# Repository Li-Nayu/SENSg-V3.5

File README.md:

SENSg-V3.5
==========
<h4>National Science Experiment: SENsg,  Large-scale Internet of Things Sensor Deployment in SUTD, Singapore</h4>

#Overview
V3.5 of SENSg is developed during my exchange period in SUTD, Singapore. Thanks to Professor Wilhelm Erik's kind guidance.

#Change Log
* Add P-channel MOSFET as the power switch for camera. MOSFET is controlled by MCU pin1, which is also the LDR sensor's GPIO pin. 
* With a pull-up resistor, the camera won't on unless the pin1 gives a low voltage. Also the camera's VCC input is changed to MOSFET's source.
* All changes were tested.

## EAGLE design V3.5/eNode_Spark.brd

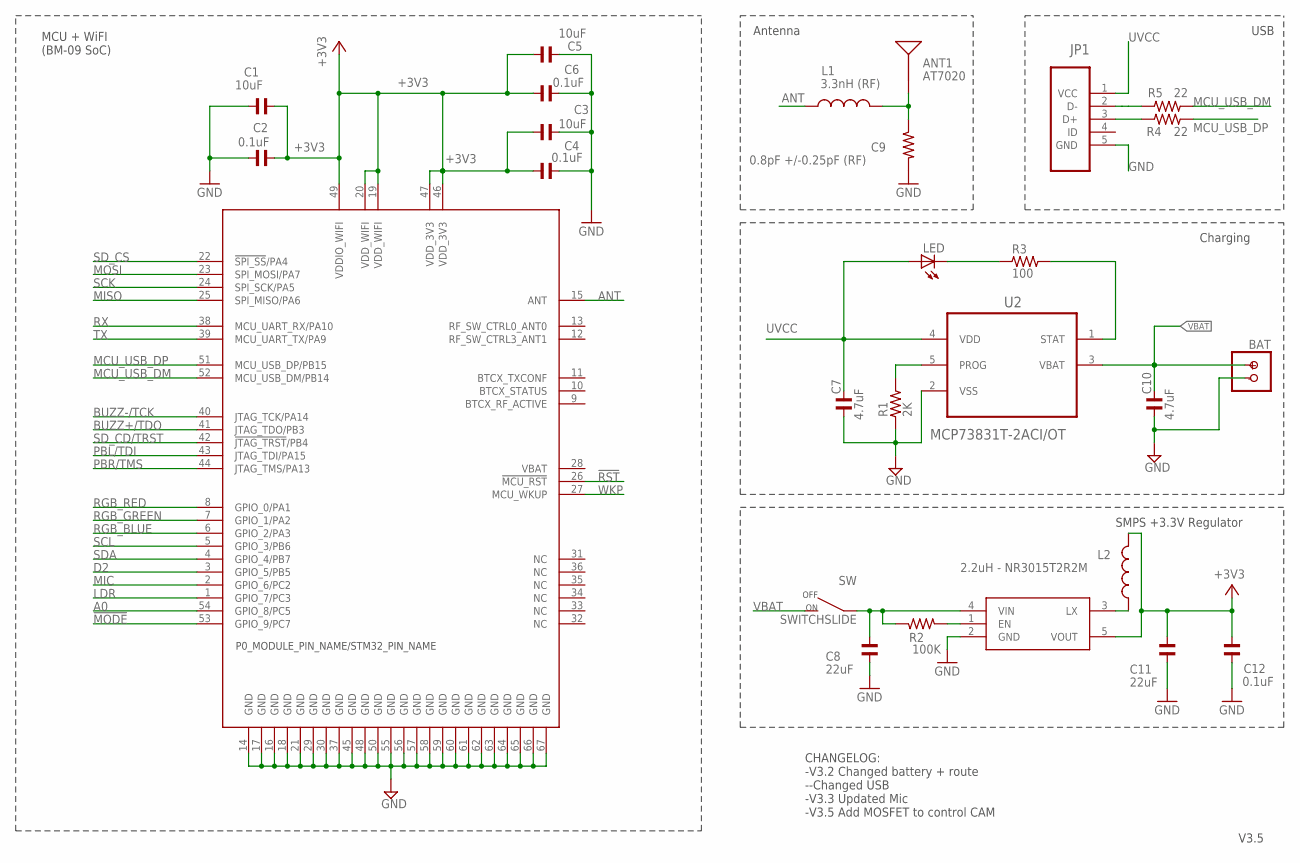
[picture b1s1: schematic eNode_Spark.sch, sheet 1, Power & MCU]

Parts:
ANT1: AT7020
BAT: BATTERYSMT; JST-2-SMD
C1, C3, C5: 10uF; C0402
C2, C4, C6, C12: 0.1uF; C0402
C7, C10: 4.7uF; C0402
C8, C11: 22uF; C0603
C9: 0.8pF +/-0.25pF (RF); R0402_B
JP1: 47346-0001; MOLEX_47346-0001
L1: 3.3nH (RF); L0402_B
L2: 2.2uH - NR3015T2R2M; INDUCTOR-NR3015
LED: LED; SMARTLED-TTW
R1: 2K; R0603
R2: 100K; R0402
R3: 100; R0603
R4, R5: 22; R0402
SW: SWITCHSLIDE; CHANGE_OVER_SLIDE
U1: WM-N-BM-09
U2: MCP73831T-2ACI/OT; SOT95P280X145-5N
U3: R8008-33; SOT23-5

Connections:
!MODE: U1.53 (GPIO_9/PC7); also elsewhere on the board
!RST: U1.26 (!MCU_RST); also elsewhere on the board
+3V3: C1.2, C2.2, C3.1, C4.2, C5.1, C6.2, C11.1, C12.1, L2.2, U1.19 (VDD_WIFI), U1.20 (VDD_WIFI), U1.46 (VDD_3V3), U1.47 (VDD_3V3), U1.49 (VDDIO_WIFI), U3.5 (VOUT); also elsewhere on the board
A0: U1.54 (GPIO_8/PC5)
ANT: L1.1, U1.15 (ANT)
BUZZ+/TDO: U1.41 (JTAG_TDO/PB3); also elsewhere on the board
BUZZ-/TCK: U1.40 (JTAG_TCK/PA14); also elsewhere on the board
D2: U1.3 (GPIO_5/PB5); also elsewhere on the board
ENABLE: R2.1, U3.1 (EN)
GND: BAT.-, C1.1, C2.1, C3.2, C4.1, C5.2, C6.1, C7.1, C8.2, C9.2, C10.1, C11.2, C12.2, JP1.5 (GND), R1.1, U1.14 (GND), U1.16 (GND), U1.17 (GND), U1.18 (GND), U1.21 (GND), U1.29 (GND), U1.30 (GND), U1.37 (GND), U1.45 (GND), U1.48 (GND), U1.50 (GND), U1.55 (GND), U1.56 (GND), U1.57 (GND), U1.58 (GND), U1.59 (GND), U1.60 (GND), U1.61 (GND), U1.62 (GND), U1.63 (GND), U1.64 (GND), U1.65 (GND), U1.66 (GND), U1.67 (GND), U2.2 (VSS), U3.2 (GND); also elsewhere on the board
LDR: U1.1 (GPIO_7/PC3); also elsewhere on the board
MCU_USB_DM: R5.1, U1.52 (MCU_USB_DM/PB14)
MCU_USB_DP: R4.1, U1.51 (MCU_USB_DP/PB15)
MIC: U1.2 (GPIO_6/PC2); also elsewhere on the board
MISO: U1.25 (SPI_MISO/PA6); also elsewhere on the board
MOSI: U1.23 (SPI_MOSI/PA7); also elsewhere on the board
unnamed: ANT1.1, C9.1, L1.2
unnamed: C8.1, R2.2, SW.1, U3.4 (VIN)
unnamed: L2.1, U3.3 (LX)
unnamed: R1.2, U2.5 (PROG)
unnamed: LED.C@1 (C), R3.1
unnamed: R3.2, U2.1 (STAT)
unnamed: JP1.3 (D+), R4.2
unnamed: JP1.2 (D-), R5.2
PBL/TDI: U1.43 (JTAG_TDI/PA15); also elsewhere on the board
PBR/TMS: U1.44 (JTAG_TMS/PA13); also elsewhere on the board
RGB_BLUE: U1.6 (GPIO_2/PA3); also elsewhere on the board
RGB_GREEN: U1.7 (GPIO_1/PA2); also elsewhere on the board
RGB_RED: U1.8 (GPIO_0/PA1); also elsewhere on the board
RX: U1.38 (MCU_UART_RX/PA10); also elsewhere on the board
SCK: U1.24 (SPI_SCK/PA5); also elsewhere on the board
SCL: U1.5 (GPIO_3/PB6); also elsewhere on the board
SDA: U1.4 (GPIO_4/PB7); also elsewhere on the board
SD_CD/TRST: U1.42 (!JTAG_TRST!/PB4); also elsewhere on the board
SD_CS: U1.22 (!SPI_SS!/PA4); also elsewhere on the board
TX: U1.39 (MCU_UART_TX/PA9); also elsewhere on the board
UVCC: C7.2, JP1.1 (VCC), LED.A@1 (A), U2.4 (VDD)
VBAT: BAT.+, C10.2, SW.2, U2.3 (VBAT)
WKP: U1.27 (MCU_WKUP); also elsewhere on the board

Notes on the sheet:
V3.5
CHANGELOG: -V3.2 Changed battery + route --Changed USB -V3.3 Updated Mic -V3.5 Add MOSFET to control CAM
USB
MCU + WiFI (BM-09 SoC)
Charging
Antenna
SMPS +3.3V Regulator

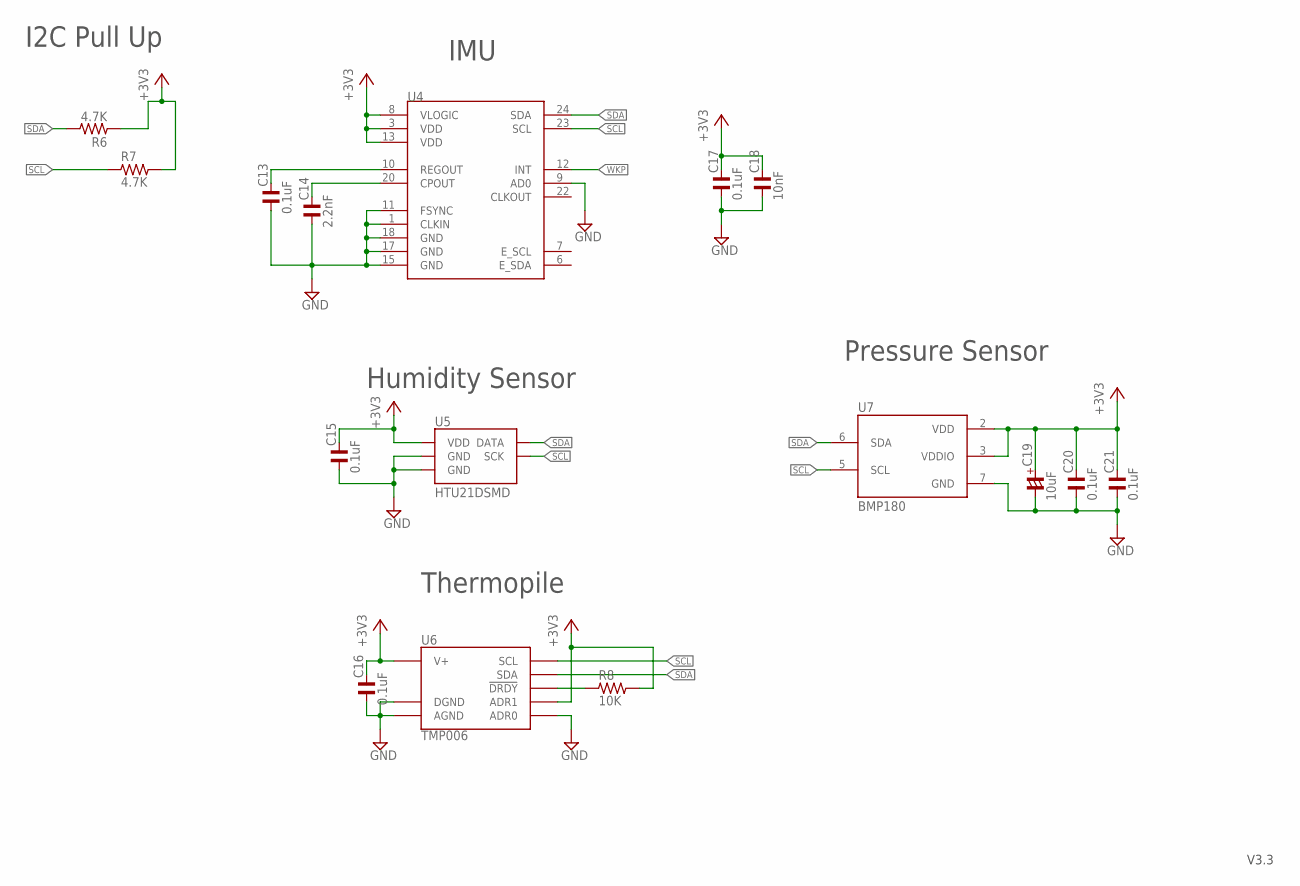
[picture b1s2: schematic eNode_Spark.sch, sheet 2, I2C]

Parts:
C13, C15, C16, C17, C20, C21: 0.1uF; C0402
C14: 2.2nF; C0402
C18: 10nF; C0402
C19: 10uF; C1206/T
R6, R7: 4.7K; R0402
R8: 10K; R0603
U4: MPU-9150QFN-24-NP; QFN-24-NP
U5: HTU21DSMD; HTU21D
U6: TMP006; BGA8DS
U7: BMP180

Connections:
+3V3: C15.2, C16.2, C17.2, C18.2, C19.+, C20.2, C21.2, R6.1, R7.2, R8.2, U4.3 (VDD), U4.8 (VLOGIC), U4.13 (VDD), U5.VDD, U6.A3 (V+), U6.B1 (ADR1), U7.2 (VDD), U7.3 (VDDIO); also elsewhere on the board
GND: C13.1, C14.1, C15.1, C16.1, C17.1, C18.1, C19.-, C20.1, C21.1, U4.1 (CLKIN), U4.9 (AD0), U4.11 (FSYNC), U4.15 (GND), U4.17 (GND), U4.18 (GND), U5.7 (GND), U5.GND, U6.A1 (DGND), U6.A2 (AGND), U6.C1 (ADR0), U7.7 (GND); also elsewhere on the board
unnamed: C14.2, U4.20 (CPOUT)
unnamed: C13.2, U4.10 (REGOUT)
unnamed: R8.1, U6.C2 (!DRDY)
SCL: R7.1, U4.23 (SCL), U5.SCK, U6.B3 (SCL), U7.5 (SCL); also elsewhere on the board
SDA: R6.2, U4.24 (SDA), U5.DATA, U6.C3 (SDA), U7.6 (SDA); also elsewhere on the board
WKP: U4.12 (INT); also elsewhere on the board

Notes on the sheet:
IMU
Humidity Sensor
Pressure Sensor
Thermopile
I2C Pull Up

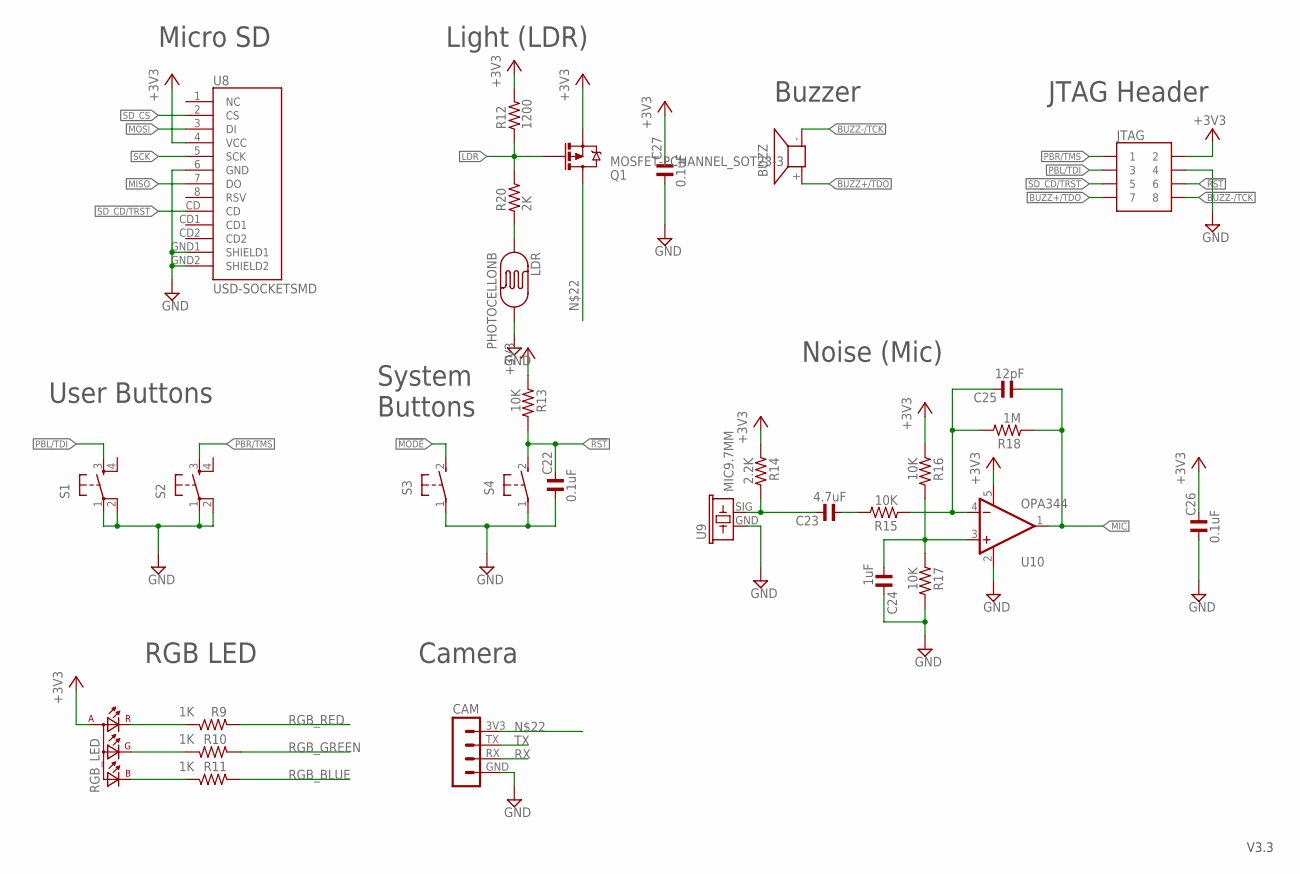
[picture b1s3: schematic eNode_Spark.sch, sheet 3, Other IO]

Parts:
BUZZ: BUZZER; OFFBOARD_NOSIGN
C22, C26, C27: 0.1uF; C0402
C23: 4.7uF; C0402
C24: 1uF; C0402
C25: 12pF; C0402
CAM: MA04-1
JTAG: JTAG_CONNECTOR; JTAG_DIP
LDR: PHOTOCELLONB; ON_BOARD
Q1: MOSFET-PCHANNEL_SOT23-3; SOT23-3
R9, R10, R11: 1K; R0402
R12: 1200; R0603
R13, R15, R16, R17: 10K; R0402
R14: 2.2K; R0402
R18: 1M; R0402
R20: 2K; R0603
RGB_LED: TOPLED-3PLCC; P-LCC-4-3
S1, S2: TAC_SWITCH_4SMD; TACTILE_SWITCH_SMD_LARGE_4
S3: MODE; DTSM-3
S4: RESET; DTSM-3
U8: USD-SOCKETSMD; MICRO-SD-SOCKET-PP
U9: MIC9.7MM; MIC-9.7MM
U10: OPA344; SOT23-5

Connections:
!MODE: S3.2; also elsewhere on the board
!RST: C22.2, JTAG.6, R13.2, S4.2; also elsewhere on the board
+3V3: C26.2, C27.2, JTAG.2, Q1.2 (S), R12.2, R13.1, R14.1, R16.1, RGB_LED.A (A2), U8.4 (VCC), U10.5 (V+); also elsewhere on the board
BUZZ+/TDO: BUZZ.+, JTAG.7; also elsewhere on the board
BUZZ-/TCK: BUZZ.-, JTAG.8; also elsewhere on the board
GND: C22.1, C24.2, C26.1, C27.1, CAM.GND, JTAG.4, LDR.2, R17.2, S1.1, S1.2, S2.1, S2.2, S3.1, S4.1, U8.6 (GND), U8.GND1 (SHIELD1), U8.GND2 (SHIELD2), U9.GND, U10.2 (V-); also elsewhere on the board
LDR: Q1.1 (G), R12.1, R20.2; also elsewhere on the board
MIC: C25.1, R18.1, U10.1 (OUT); also elsewhere on the board
MISO: U8.7 (DO); also elsewhere on the board
MOSI: U8.3 (DI); also elsewhere on the board
unnamed: C23.1, R15.2
unnamed: C25.2, R15.1, R18.2, U10.4 (-IN)
unnamed: C24.1, R16.2, R17.1, U10.3 (+IN)
unnamed: C23.2, R14.2, U9.SIG
unnamed: LDR.1, R20.1
unnamed: CAM.3V3, Q1.3 (D)
unnamed: R10.1, RGB_LED.G (CGREEN)
unnamed: R11.1, RGB_LED.B (CBLUE)
unnamed: R9.1, RGB_LED.R (CRED)
PBL/TDI: JTAG.3, S1.3; also elsewhere on the board
PBR/TMS: JTAG.1, S2.3; also elsewhere on the board
RGB_BLUE: R11.2; also elsewhere on the board
RGB_GREEN: R10.2; also elsewhere on the board
RGB_RED: R9.2; also elsewhere on the board
RX: CAM.RX; also elsewhere on the board
SCK: U8.5 (SCK); also elsewhere on the board
SD_CD/TRST: JTAG.5, U8.CD; also elsewhere on the board
SD_CS: U8.2 (CS); also elsewhere on the board
TX: CAM.TX; also elsewhere on the board

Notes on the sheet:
Micro SD
User Buttons
Light (LDR)
Buzzer
Noise (Mic)
RGB LED
Camera
System Buttons
JTAG Header

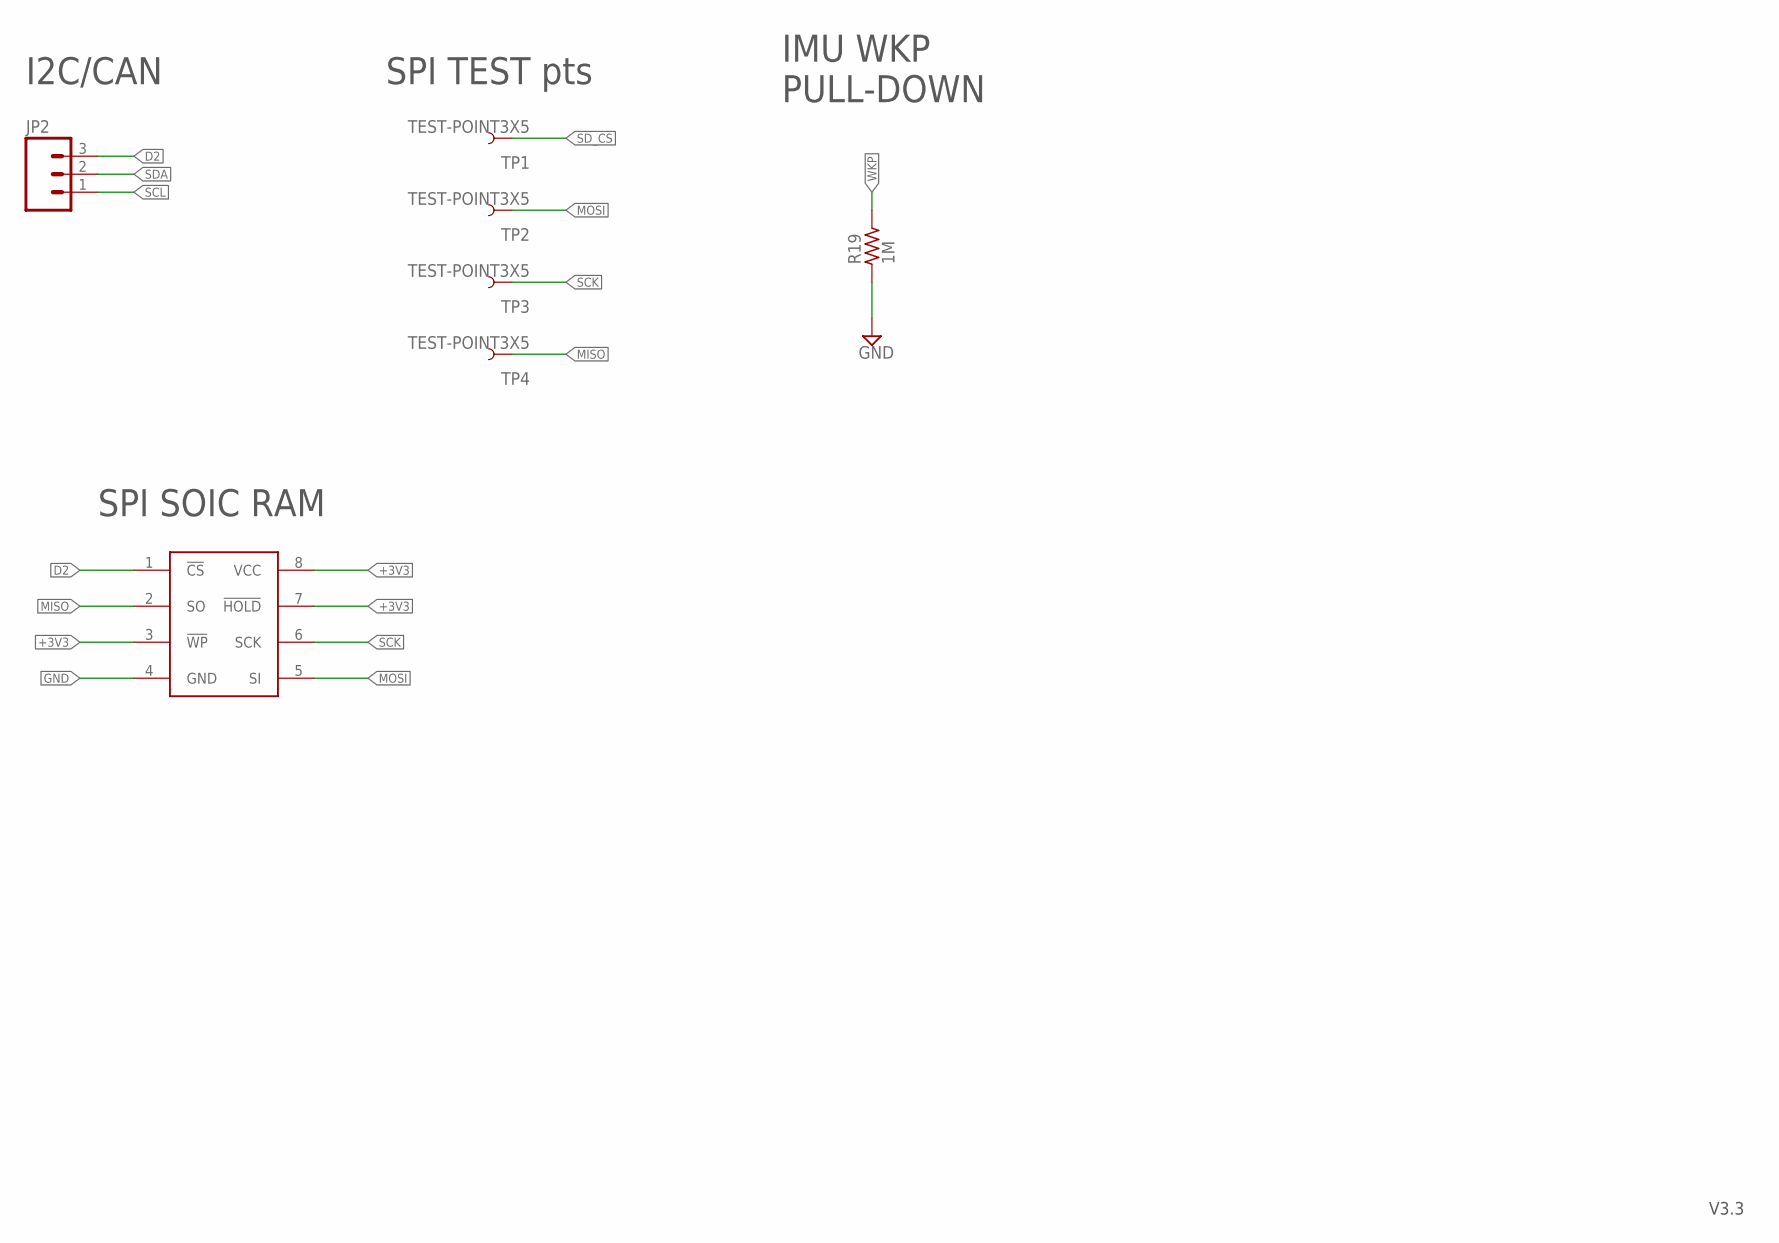
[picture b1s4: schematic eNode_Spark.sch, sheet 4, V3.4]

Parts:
JP2: M03PTH; 1X03
R19: 1M; R0402
TP1, TP2, TP3, TP4: TEST-POINT3X5; PAD.03X.05
U11: FRAM; SO08

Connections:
+3V3: U11.3 (!WP), U11.7 (!HOLD), U11.8 (VCC); also elsewhere on the board
D2: JP2.3, U11.1 (!CS); also elsewhere on the board
GND: R19.1, U11.4 (GND); also elsewhere on the board
MISO: TP4.P$1, U11.2 (SO); also elsewhere on the board
MOSI: TP2.P$1, U11.5 (SI); also elsewhere on the board
SCK: TP3.P$1, U11.6 (SCK); also elsewhere on the board
SCL: JP2.1; also elsewhere on the board
SDA: JP2.2; also elsewhere on the board
SD_CS: TP1.P$1; also elsewhere on the board
WKP: R19.2; also elsewhere on the board

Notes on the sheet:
I2C/CAN
SPI TEST pts
SPI SOIC RAM
IMU WKP PULL-DOWN

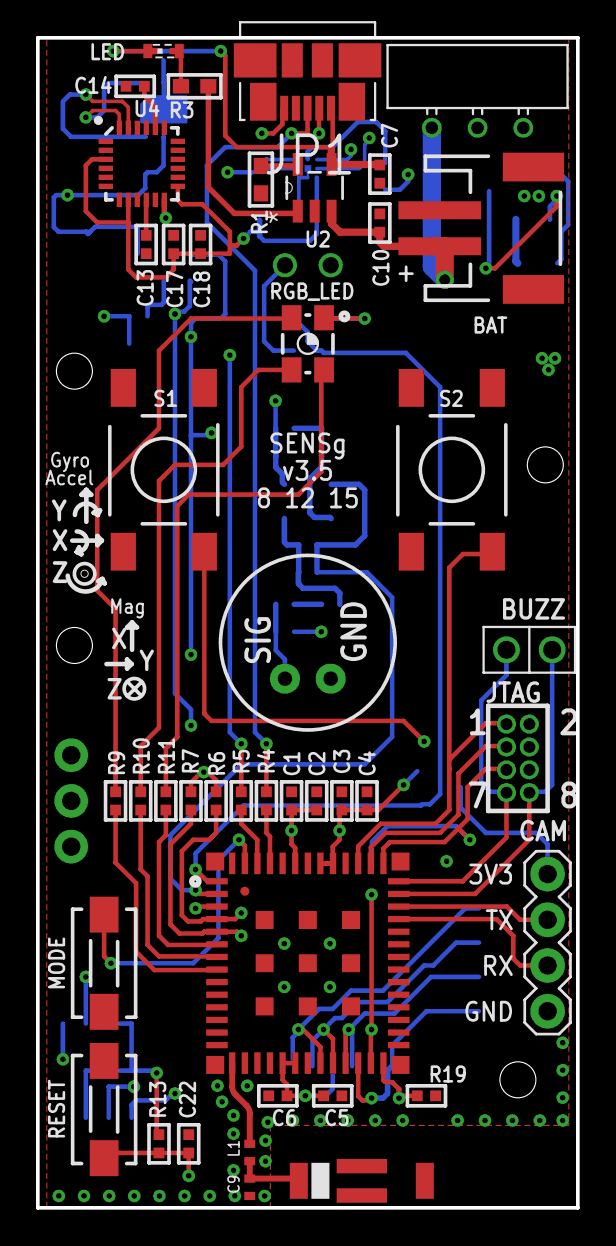
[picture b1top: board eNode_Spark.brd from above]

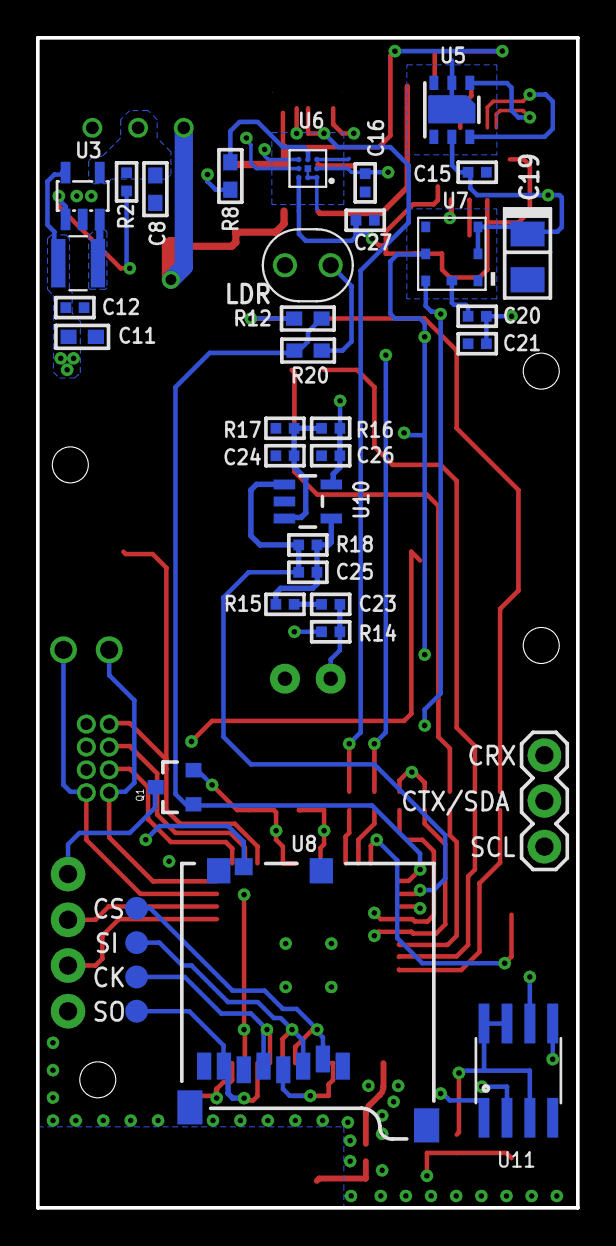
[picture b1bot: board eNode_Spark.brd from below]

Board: 4 copper layers, 30.0 x 65.0 mm, 80 parts (37 on the bottom side), 50 nets.

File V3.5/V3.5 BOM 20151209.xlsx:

Sub-System | Description & Link | Category | Supplier | DELTA Sourcing | Package / Case | Supplier | Supplier Part # | Units /Piece | Reference on the PCB
Power & Charging | 1800 mAh Li-Po Battery | Battery |  | V |  | Data Power |  | 1 |  |  |  |  | USD Conv.
 | 3.3v DC/DC converter | IC | Richtek | V | SOT-23 | Digikey | RT8008-33GB-ND | 1 | U3
 | MCP73831T (Charging) | IC | Microchip | FIX | SOT-5 | Element14 | 1332158 | 1 | U2
 | MICRO USB | Connector | MOLEX | V |  | Element14 | 1568026 | 1 | JP1
 | 4.7 uF | MLCC | Murata | V | 402 | Element14 | 2426952 | 2 | C7,C10
 | 2K OHM | Resistor | Murata | V | 603 | Element14 | 1469764 | 1 | R1
 | 100 OHM | Resistor | Yageo | V | 603 | Element14 | 9233253 | 1 | R3
 | Indicator LED SMT | LED | Everlight | V | RA_SMD_LED | Element14 | 2146470 | 1 | LED
 | 0.1 uF (0402) | MLCC | MLCC | V | 402 | Element14 | 1759380RL | 1 | C12
 | 22uf | MLCC |  | V | 603 | Element14 | 2354098 | 2 | C8,C11
 | 100K 1% | Resistor | Multicomp | V | 402 | Element14 | 2073962 | 1 | R2
 | JST Header 2-way SMT | Connector | JST | V |  | Element14 | 9492615 | 1 | BAT
 | Inductor 2.2 uH | Inductor | Taiyo Yuden | V | INDUCTOR-NR3015 | Mouser | 963-NR3015T2R2M | 1 | L2
Main PCB components | BM-09 | MCU+WIFI | USI | FIX |  | EDOM/USI |  | 1 | U1 |  |  |  | USD Conv.
 | 0.1 uF (0402) | MLCC | MLCC | V | 402 | Element14 | 1759380RL | 4 | C2,C4,c6,C22
 | 10 uF (0402) | MLCC | MLCC | V | 402 | Element14 | 2346872 | 3 | C1,C3,C5
 | 10K OHM 1% | Resistor | Multicomp | V | 402 | Element14 | 2073960 | 1 | R13
 | SMD Tactice Button | Switch | Tyco | V | TACTILE_SWITCH_SMD_LARGE_4 | Element14 | 2410652 | 2 | S1,S2
 | Reset Switch | Switch | Multicomp | V | DTSM-3 | Element14 | 9471898 | 2 | S3,S4
 | Switch | Switch | EAO | V |  | Element14 | 1634623 | 1 | SW
 | 4.7K OHM 1% | Resistor | Multicom | V | 402 | Element14 | 1358060 | 2 | R6,R7
 | RGB LED | LED | CREE | V |  | Element14 | 2414451 | 1 | RGB_LED
 | Chip Antenna | RF Antenna | Johanson | FIX |  | Digikey | 712-1010-2-ND | 1 | ANT1
 | 0.8pF RF CAP | MLCC | Murata | V | 0402_B | Digikey | 490-6080-2-ND | 1 | C9
 | 3.3nH RF IND | Inductor | TBA | V | 0402_B | MFG: Hong Kong SUNLORD Co.,Ltd. | PN: HCI1005F-3N3J | 1 | L1
 | 1K OHM | Resistor | Multicomp | V | 402 | Element14 | 2130354 | 3 | R9,10,R11
 | 22 ohm | Resistor | Multicomp | V | 402 | Element14 | 1357998 | 2 | R4,R5
SD | Micro SD Card Slot |  | TBA | V |  |  |  | 1 | U8
 | Micro SD Card 8GB | IC | TBA | FIX |  | Alibaba |  | 1
IMU | MPU 9150 | MCU |  | FIX |  | Digikey | 1428-1009-2-ND | 1 | U4
 | 0.1 uF (0402) | MLCC | Multicomp | V | 402 | Element14 | 1759380RL | 2 | C13,C17
 | 10nF (0.01uF) | MLCC |  | V | 402 | Element14 | 1844133 | 1 | C18
 | 2.2nF (2200pF) | MLCC | Murata | V | 402 | Element14 | 1828884 | 1 | C14
LDR | LDR | Photoconductive Cell | EXCELITAS TECH | FIX |  | Digikey |  | 1 | KDR
 | 1.2K OHM 1% | Resistor | MULTICOMP | V | 603 | Element14 | 9330500 | 1 | R12
 | 2K OHM 1% | Resistor | MULTICOMP | V | 603 | Element14 | 9330763 | 1 | R20
Mic | Mic | IC | PROJECTS UNLIMITED | FIX | OFN-24Np | Element14 | 1193029 | 1 | U9
 | OPA344 Opamp | IC | TI | FIX | SOT-23-5 | Element14 | 9547550 | 1 | U10
 | 10K OHM 1% | Resistor | Multicomp | V | 402 | Element14 | 2073960 | 3 | R15,16,R17
 | 1M 1% | Resistor | Panasonic | V | 402 | Element14 | 2284171 | 1 | R18
 | 12pF | MLCC | Murata | V | 402 | Element14 | 1828875 | 1 | C25
 | 2.2 K ohm | Resistor | Panasonic | V | 402 | Element14 | 2302673 | 1 | R14
 | 4.7 uF | MLCC | Murata | V | 402 | Element14 | 2426952 | 1 | C23
 | 1.0 uF | MLCC | C5 | V | 402 | Element14 | 1844105 | 1 | C24
 | 0.1 uF (0402) | MLCC | Multicomp | V | 402 | Element14 | 1759380RL | 1 | 26
Humidity & Temperature | HTU21D | IC | Measurement | FIX |  |  |  | 1 | U5
 | 0.1 uF (0402) | MLCC | Multicomp | V | 402 | Element14 | 1759380RL | 1 | C15
Barometer | BMP180 | IC | Bosch | FIX |  |  | 262-BMP180 | 1 | U7
 | 10uF Tant | CAP | AVX | V | 1206 | Element14 | 2333009 | 1 | C19
 | 0.1 uF (0402) | MLCC | Multicomp | V | 402 | Element14 | 1759380RL | 2 | C20,C21
IR Temperature | TMP007 | IC | TI | FIX |  | Digikey | 296-28819-2-ND | 1 | U6
 | 10K OHM 1% | Resistor | Vishay | V | 603 | Element14 | 1469748RL | 1 | R8
 | 0.1 uF (0402) | MLCC | MLCC | V | 402 | Element14 | 1759380RL | 1 | C16
Buzzer | ID 1740 Buzzer | Buzzer | Adafruit | V |  | Adafruit | 1740 | 1 | BUZZ |  |  |  | USD Conv.
Camera | C1098 | Camera | 康大 | V |  | COMedia |  | 1 | CAM |  |  |  | JPEG serial camera. Minimum VGA quality.
 | P-CHANNEL MOSFET | MOSFET | Fairchild Semiconductor | V | SOT-23 | Element14 | 9846409 | 1 | Q1
 | Header | Connector | Molex | V |  | element14 | 9731091 | 1
Additional components | Case (thermoplastic injection molded) |  |  |  |  |  |  | 1
Programming Board | JTAG header | Connector | FCI | v |  | Element14 | 1865284 | 1 | Jtag

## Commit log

2015-12-14 better design
2016-01-04 Changed to Micro USB B.lbr

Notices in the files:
parts and their libraries:
rc-master-smd: Copyright (C) 2007-2008, Bob Starr
SparkFun-Connectors: Licensing: Creative Commons ShareAlike 4.0 International - https://creativecommons.org/licenses/by-sa/4.0
